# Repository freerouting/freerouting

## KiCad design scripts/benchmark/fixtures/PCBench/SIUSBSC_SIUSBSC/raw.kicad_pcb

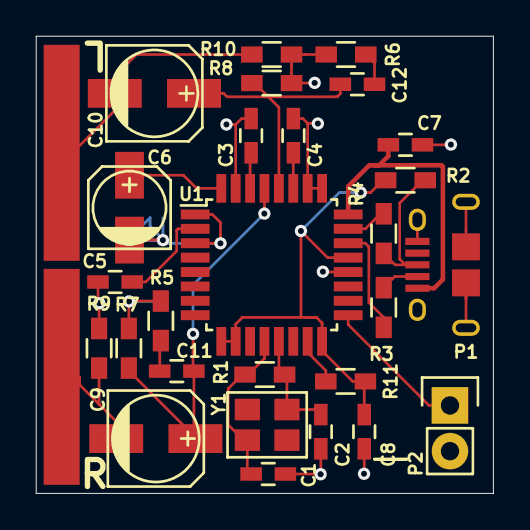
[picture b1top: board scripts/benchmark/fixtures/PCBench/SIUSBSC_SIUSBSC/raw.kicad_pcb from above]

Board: 2 copper layers, 25.4 x 25.4 mm, 30 parts (1 on the bottom side), 21 nets.

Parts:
C1, C2: 18pF; C_0603_HandSoldering
C3, C4, C5, C7, C8: 1uF; C_0603_HandSoldering
C6: 10uF; c_elec_4x5.3
C9, C10: 100uF; c_elec_5x5.3
C11, C12: 0.022uF; C_0603_HandSoldering
P1: USB_MICRO_B; CONN_USB_MICRO_B_FCI_10118194
P2: I2S; Pin_Header_Straight_1x02
P3: RIGHT; PAD_12.00x2.00mm
P4: LEFT; PAD_12.00x2.00mm
P5: GND; PAD_24.00x2.00mm
R1: 1M; R_0603_HandSoldering
R2, R11: 1K5; R_0603_HandSoldering
R3, R4: 22R; R_0603_HandSoldering
R5, R6: 16R; R_0603_HandSoldering
R7, R8, R9, R10: 3K3; R_0603_HandSoldering
U1: PCM2706; TQFP-32_7x7mm_Pitch0.8mm
Y1: 12MHz; XTAL_SMD_3225

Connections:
/D+: R4.2, U1.23
/D-: R3.2, U1.22
/DOUT: P2.1, U1.17
/DT: R11.1, U1.15
/FOUTL: C10.2, P4.1, R10.1
/FOUTR: C9.2, P3.1, R9.1
/USB_D+: P1.3, R2.2, R4.1
/USB_D-: P1.2, R3.1
/VBUS: C7.2, P1.1, U1.24
/VCCL: C4.1, U1.27
/VCCP: C5.2, U1.2
/VCCR: C3.1, U1.30
/VCOM: C6.1, U1.32
/VOUTL: C10.1, C12.1, R8.1, U1.28
/VOUTR: C9.1, C11.1, R7.1, U1.29
/XTI: C1.1, R1.2, U1.12, Y1.1
/XTO: C2.1, R1.1, U1.13, Y1.3
GND: C1.2, C2.2, C3.2, C4.2, C5.1, C6.2, C7.1, C8.2, P1.5, P1.6, P2.2, P5.1, R5.2, R6.2, R7.2, R8.2, R9.2, R10.2, U1.1, U1.3, U1.20, U1.25, U1.26, U1.31
unnamed: C11.2, R5.1
unnamed: C12.2, R6.1
VDD: C8.1, R2.1, R11.2, U1.9, U1.10, U1.16, U1.21

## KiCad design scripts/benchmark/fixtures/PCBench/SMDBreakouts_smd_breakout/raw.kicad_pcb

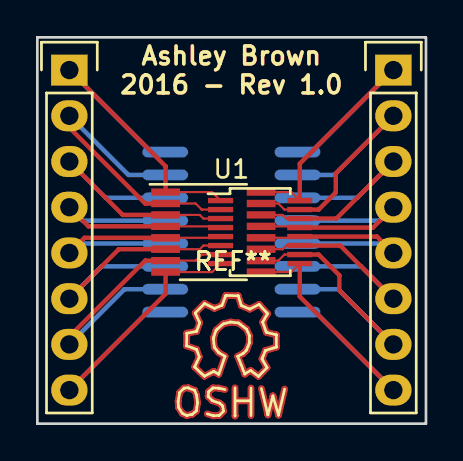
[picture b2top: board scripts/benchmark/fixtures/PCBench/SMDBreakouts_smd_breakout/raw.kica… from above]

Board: 2 copper layers, 21.6 x 21.5 mm, 4 parts (1 on the bottom side), 16 nets.

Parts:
P1, P3: CONN_01X08; Pin_Header_Straight_1x08
U1: Generic_16Pin_Chip; MSOP-16_3x4mm_Pitch0.5mm
U1#2: Generic_16Pin_Chip; SOIC-16_3.9x9.9mm_Pitch1.27mm

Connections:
unnamed: P1.1, U1.1, U1#2.16
unnamed: P1.2, U1.2, U1#2.15
unnamed: P1.3, U1.3, U1#2.14
unnamed: P1.4, U1.4, U1#2.13
unnamed: P1.5, U1.5, U1#2.12
unnamed: P1.6, U1.6, U1#2.11
unnamed: P1.7, U1.7, U1#2.10
unnamed: P1.8, U1.8, U1#2.9
unnamed: P3.1, U1.16, U1#2.1
unnamed: P3.2, U1.15, U1#2.2
unnamed: P3.3, U1.14, U1#2.3
unnamed: P3.4, U1.13, U1#2.4
unnamed: P3.5, U1.12, U1#2.5
unnamed: P3.6, U1.11, U1#2.6
unnamed: P3.7, U1.10, U1#2.7
unnamed: P3.8, U1.9, U1#2.8

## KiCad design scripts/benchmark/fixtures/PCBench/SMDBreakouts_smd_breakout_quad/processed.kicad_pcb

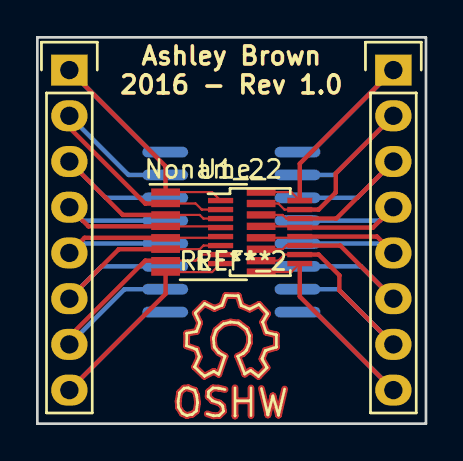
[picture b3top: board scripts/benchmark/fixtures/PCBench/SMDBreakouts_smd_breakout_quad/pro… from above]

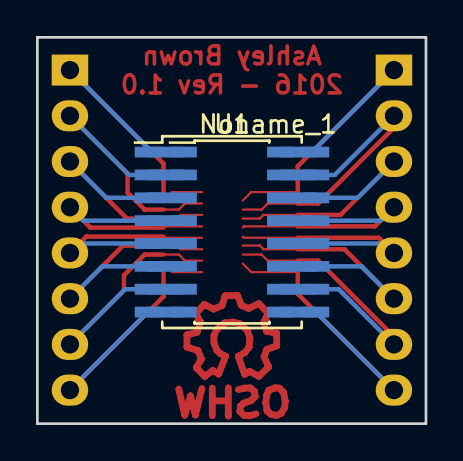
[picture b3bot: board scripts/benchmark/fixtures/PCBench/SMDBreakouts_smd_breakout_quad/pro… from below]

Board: 2 copper layers, 21.6 x 21.5 mm, 6 parts (2 on the bottom side), 16 nets.

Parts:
Noname_1: Generic_16Pin_Chip; SOIC-16_7.5x10.3mm_Pitch1.27mm
Noname_2: Generic_16Pin_Chip; QSOP-16_3.9x4.9mm_Pitch0.635mm
P1, P3: CONN_01X08; Pin_Header_Straight_1x08
U1: Generic_16Pin_Chip; SOIC-16_3.9x9.9mm_Pitch1.27mm
U1_2: Generic_16Pin_Chip; MSOP-16_3x4mm_Pitch0.5mm

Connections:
unnamed: Noname_1.16, Noname_2.1, P1.1, U1.16, U1_2.1
unnamed: Noname_1.15, Noname_2.2, P1.2, U1.15, U1_2.2
unnamed: Noname_1.14, Noname_2.3, P1.3, U1.14, U1_2.3
unnamed: Noname_1.13, Noname_2.4, P1.4, U1.13, U1_2.4
unnamed: Noname_1.12, Noname_2.5, P1.5, U1.12, U1_2.5
unnamed: Noname_1.11, Noname_2.6, P1.6, U1.11, U1_2.6
unnamed: Noname_1.10, Noname_2.7, P1.7, U1.10, U1_2.7
unnamed: Noname_1.9, Noname_2.8, P1.8, U1.9, U1_2.8
unnamed: Noname_1.1, Noname_2.16, P3.1, U1.1, U1_2.16
unnamed: Noname_1.2, Noname_2.15, P3.2, U1.2, U1_2.15
unnamed: Noname_1.3, Noname_2.14, P3.3, U1.3, U1_2.14
unnamed: Noname_1.4, Noname_2.13, P3.4, U1.4, U1_2.13
unnamed: Noname_1.5, Noname_2.12, P3.5, U1.5, U1_2.12
unnamed: Noname_1.6, Noname_2.11, P3.6, U1.6, U1_2.11
unnamed: Noname_1.7, Noname_2.10, P3.7, U1.7, U1_2.10
unnamed: Noname_1.8, Noname_2.9, P3.8, U1.8, U1_2.9

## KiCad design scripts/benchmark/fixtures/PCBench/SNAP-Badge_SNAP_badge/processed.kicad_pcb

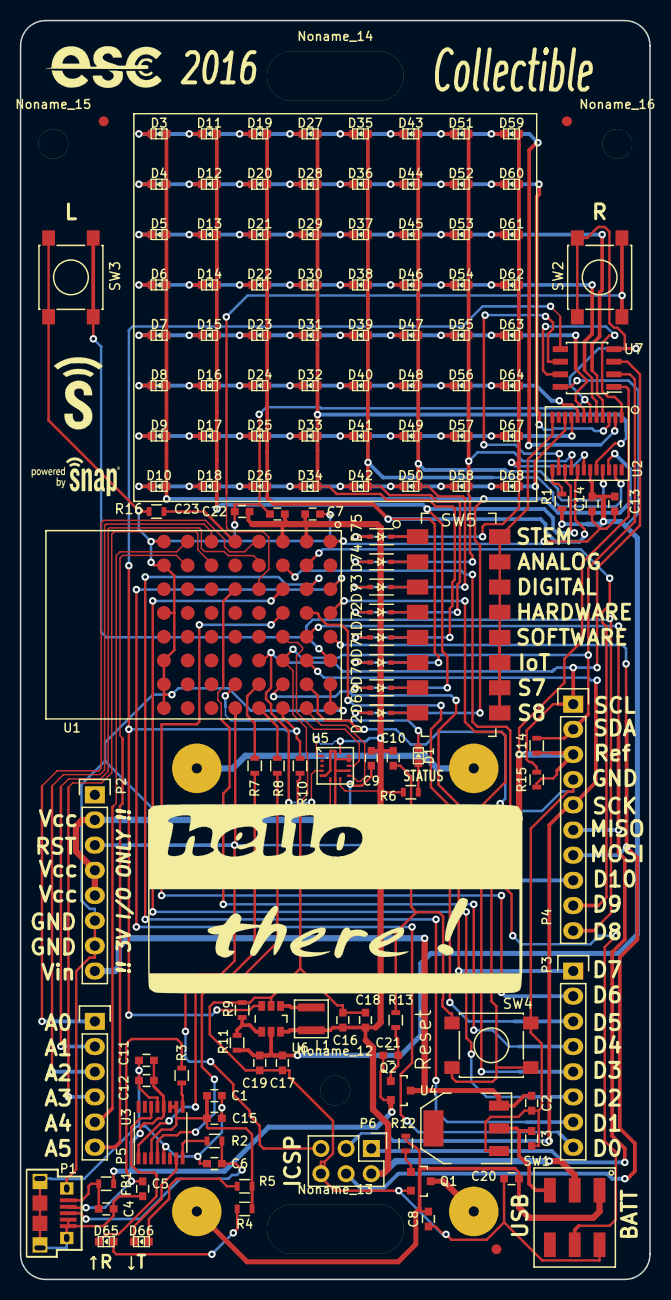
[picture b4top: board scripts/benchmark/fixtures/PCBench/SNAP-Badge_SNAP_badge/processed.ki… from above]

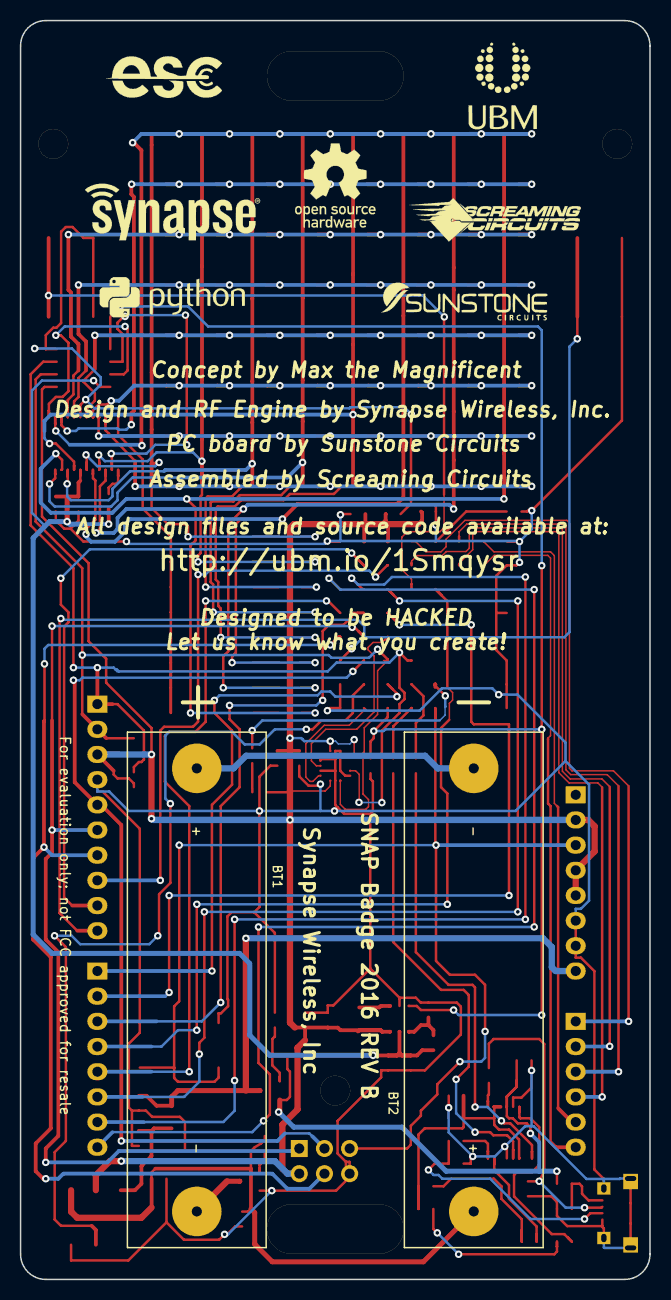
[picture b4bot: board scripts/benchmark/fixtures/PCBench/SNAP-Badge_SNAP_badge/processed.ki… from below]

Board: 2 copper layers, 63.5 x 127.0 mm, 157 parts (9 on the bottom side), 86 nets.

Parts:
BT1, BT2: 1.5V; BATT_2466
C1, C2, C10, C12, C14, C18, C20, C21: 0.1uF; C_0603
C3, C16: 10uF; C_0603
C4: 10nF; C_0603
C5, C6: 47pF; C_0603
C7, C8, C22, C23: 22uF; C_0603
C9, C11, C13, C15, C17, C19: 4.7uF; C_0603
D1, D3, D4, D5, D6, D7, D8, D9, D10, D11, D12, D13, D14, D15, D16, D17, D18, D19, D20, D21, D22, D23, D24, D25, D26, D27, D28, D29, D30, D31, D32, D33, D34, D35, D36, D37, D38, D39, D40, D41, D42, D43, D44, D45, D46, D47, D48, D49, D50, D51, D52, D53, D54, D55, D56, D57, D58, D59, D60, D61, D62, D63, D64, D65, D66, D67, D68: LED; Led_0603
D2, D69, D70, D71, D72, D73, D74, D75: 1N4148W; SOD-323
FB1: 600 OHM 500MA; R_0603
Fiducial_Mark: VAL**; Fiducial_Mark
Fiducial_Mark_2, Fiducial_Mark_3: VAL**; Fiducial_Mark
L1: 4.7uH 0.9A; TYS-2
Noname_1: LOGO; Hello
Noname_2: LOGO; UBM_logo
Noname_3: LOGO; Sunstone_logo
Noname_4: LOGO; Screaming_logo
Noname_5: LOGO; Synapse_logo
Noname_6: LOGO; Python_logo
Noname_7: OSHW_logo
Noname_8, Noname_11: ESC_logo
Noname_9: syn_logo1_8x8
Noname_10: pb_snap
Noname_12, Noname_15, Noname_16: MountingHole_3mm
Noname_13, Noname_14: LanyardSlot
P1: MicroB; USBmicroB
P2, P3: CONN_01X08; Socket_Strip_Straight_1x08
P4: CONN_01X10; Socket_Strip_Straight_1x10
P5: CONN_01X06; Socket_Strip_Straight_1x06
P6: CONN_02X03; Pin_Header_Straight_2x03
Q1: ZXMN2F30FHCT-ND; SOT-23
Q2: Si2305DS; SOT-23
R1: 10k; R_0603
R2, R3: 27; R_0603
R4, R5, R6: 270; R_0603
R7, R8: 1k; R_0603
R9: 200k; R_0603
R10, R12: 100k; R_0603
R11: 1M; R_0603
R13: 39k; R_0603
R14, R15, R16: 4.7k; R_0603
SW1: SWITCH_DPDT; SO-DPDT-6
SW2, SW3, SW4: SW_PUSH; SW_SPST_PTS645
SW5: SW_DIP_8; DIPSW-16
U1: SM220
U2: AS1115; QSOP-24
U3: FT230XS; SSOP-16_3.9x4.9mm_Pitch0.635mm
U4: LD1117S33CTR; SOT-223
U5: LIS3DH; LGA16_3x3
U6: TPS61070; TSOT-6-MK06A
U7: NLSX4373; SOIC-8_3.9x4.9mm_Pitch1.27mm

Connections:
/*IS_USB: SW1.5, U1.G2
/*RESET: P2.3, P6.5, SW4.2, U1.H5
/ACC_INT1: U1.E3, U5.11
/ACC_INT2: U1.H2, U5.9
/BTN_LFT: P4.10, SW3.2, U1.F1
/BTN_RT: SW2.2, U1.C4
/LED_matrix/DIG0: D3.1, D11.1, D19.1, D27.1, D35.1, D43.1, D51.1, D59.1, U2.2
/LED_matrix/DIG1: D4.1, D12.1, D20.1, D28.1, D36.1, D44.1, D52.1, D60.1, U2.3
/LED_matrix/DIG2: D5.1, D13.1, D21.1, D29.1, D37.1, D45.1, D53.1, D61.1, U2.4
/LED_matrix/DIG3: D6.1, D14.1, D22.1, D30.1, D38.1, D46.1, D54.1, D62.1, U2.5
/LED_matrix/DIG4: D7.1, D15.1, D23.1, D31.1, D39.1, D47.1, D55.1, D63.1, U2.7
/LED_matrix/DIG5: D8.1, D16.1, D24.1, D32.1, D40.1, D48.1, D56.1, D64.1, U2.8
/LED_matrix/DIG6: D9.1, D17.1, D25.1, D33.1, D41.1, D49.1, D57.1, D67.1, U2.9
/LED_matrix/DIG7: D10.1, D18.1, D26.1, D34.1, D42.1, D50.1, D58.1, D68.1, U2.10
/LED_matrix/LED_3V: C13.1, C14.1, C17.1, C19.1, R1.1, R11.1, U2.19, U6.5, U7.8
/LED_matrix/LED_SCL: U2.14, U7.6
/LED_matrix/LED_SDA: U2.1, U7.7
/LED_matrix/SEGA: D11.2, D12.2, D13.2, D14.2, D15.2, D16.2, D17.2, D18.2, D69.2, U2.15
/LED_matrix/SEGB: D19.2, D20.2, D21.2, D22.2, D23.2, D24.2, D25.2, D26.2, D70.2, U2.17
/LED_matrix/SEGC: D27.2, D28.2, D29.2, D30.2, D31.2, D32.2, D33.2, D34.2, D71.2, U2.20
/LED_matrix/SEGD: D35.2, D36.2, D37.2, D38.2, D39.2, D40.2, D41.2, D42.2, D72.2, U2.23
/LED_matrix/SEGDP: D2.2, D3.2, D4.2, D5.2, D6.2, D7.2, D8.2, D9.2, D10.2, U2.22
/LED_matrix/SEGE: D43.2, D44.2, D45.2, D46.2, D47.2, D48.2, D49.2, D50.2, D73.2, U2.21
/LED_matrix/SEGF: D51.2, D52.2, D53.2, D54.2, D55.2, D56.2, D57.2, D58.2, D74.2, U2.16
/LED_matrix/SEGG: D59.2, D60.2, D61.2, D62.2, D63.2, D64.2, D67.2, D68.2, D75.2, U2.18
/MISO: P4.6, P6.1, U1.E2
/MOSI: P4.7, P6.4, U1.E1
/PB5: P3.5, U1.D1
/PB6: P3.3, U1.D2
/PB7: P3.2, U1.D3
/PD4: P3.1, U1.G3
/PE0: P3.8, U1.C1
/PE1: P3.7, U1.C2
/PE3: P4.9, U1.B2
/PE4: P3.6, U1.C3
/PE5: P4.8, U1.B3
/PE7: P3.4, U1.C5
/PF0: P5.1, U1.A4
/PF1: P5.2, U1.B4
/PF4: P5.3, U1.A6
/PF5: P5.4, U1.B6
/PF6: P5.5, U1.A7
/PF7: P5.6, U1.B7
/RXLED: D66.1, U3.7
/SCLK: P4.5, P6.3, U1.F2
/STATUS_LED: D1.1, U1.G5
/TXLED: D65.1, U3.14
/USB_RXD: R8.2, U1.H4
/USB_TXD: R7.2, U1.G4
/VIN_USB: C11.1, C12.1, C21.1, FB1.2, Q2.2, U3.12
/VREG_IN: C2.1, P2.8, Q2.3, U4.3
GND: C1.2, C2.2, C3.2, C4.2, C5.2, C6.2, C7.2, C8.2, C9.2, C10.2, C11.2, C12.2, C13.2, C14.2, C15.2, C16.2, C17.2, C18.2, C19.2, C20.2, C22.2, C23.2, P1.4, P1.5, P1.6, P2.6, P2.7, P4.4, P6.6, Q1.2, R9.1, R10.1, R13.1, R16.2, SW1.6, SW2.1, SW3.1, SW4.1, U1.A1, U1.A8, U1.B8, U1.D8, U1.F8, U1.G1, U1.G8, U1.H1, U1.H8, U2.6, U3.5, U3.13, U4.1, U5.5, U5.7, U5.10, U5.12, U5.13, U5.15, U5.16, U6.2, U7.4
I2C_SCL: P4.1, R15.2, U1.F4, U5.4, U7.3
I2C_SDA: P4.2, R14.2, U1.F3, U5.6, U7.2
LED_PWR_EN: R10.2, U1.H3, U6.3, U7.5
unnamed: BT1.1, BT2.2
unnamed: BT1.2, Q1.3
unnamed: BT2.1, C8.1, C20.1, R12.1, SW1.1
unnamed: C1.1, C15.1, R4.1, R5.1, U3.3, U3.10, U3.11
unnamed: C3.1, SW1.3, U4.2
unnamed: C4.1, FB1.1, P1.1
unnamed: C5.1, P1.2, R3.2
unnamed: C6.1, P1.3, R2.2
unnamed: C21.2, Q2.1, R13.2
unnamed: D1.2, R6.2
unnamed: D2.1, SW5.8
unnamed: D65.2, R4.2
unnamed: D66.2, R5.2
unnamed: D69.1, SW5.7
unnamed: D70.1, SW5.6
unnamed: D71.1, SW5.5
unnamed: D72.1, SW5.4
unnamed: D73.1, SW5.3
unnamed: D74.1, SW5.2
unnamed: D75.1, SW5.1
unnamed: L1.1, U6.1
unnamed: Q1.1, R12.2
unnamed: R1.2, U2.13
unnamed: R2.1, U3.8
unnamed: R3.1, U3.9
unnamed: R7.1, U3.1
unnamed: R8.1, U3.4
unnamed: R9.2, R11.2, U6.4
unnamed: R16.1, U1.A5
unnamed: SW5.9, SW5.10, SW5.11, SW5.12, SW5.13, SW5.14, SW5.15, SW5.16, U2.12
VCC: C7.1, C9.1, C10.1, C16.1, C18.1, C22.1, C23.1, L1.2, P2.2, P2.4, P2.5, P4.3, P6.2, R6.1, R14.1, R15.1, SW1.2, U1.A2, U1.A3, U5.1, U5.8, U5.14, U6.6, U7.1
